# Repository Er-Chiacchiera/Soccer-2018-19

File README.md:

# Soccer-2018-19
Soccer Robot of Pacinotti-Archimede 2018/2019

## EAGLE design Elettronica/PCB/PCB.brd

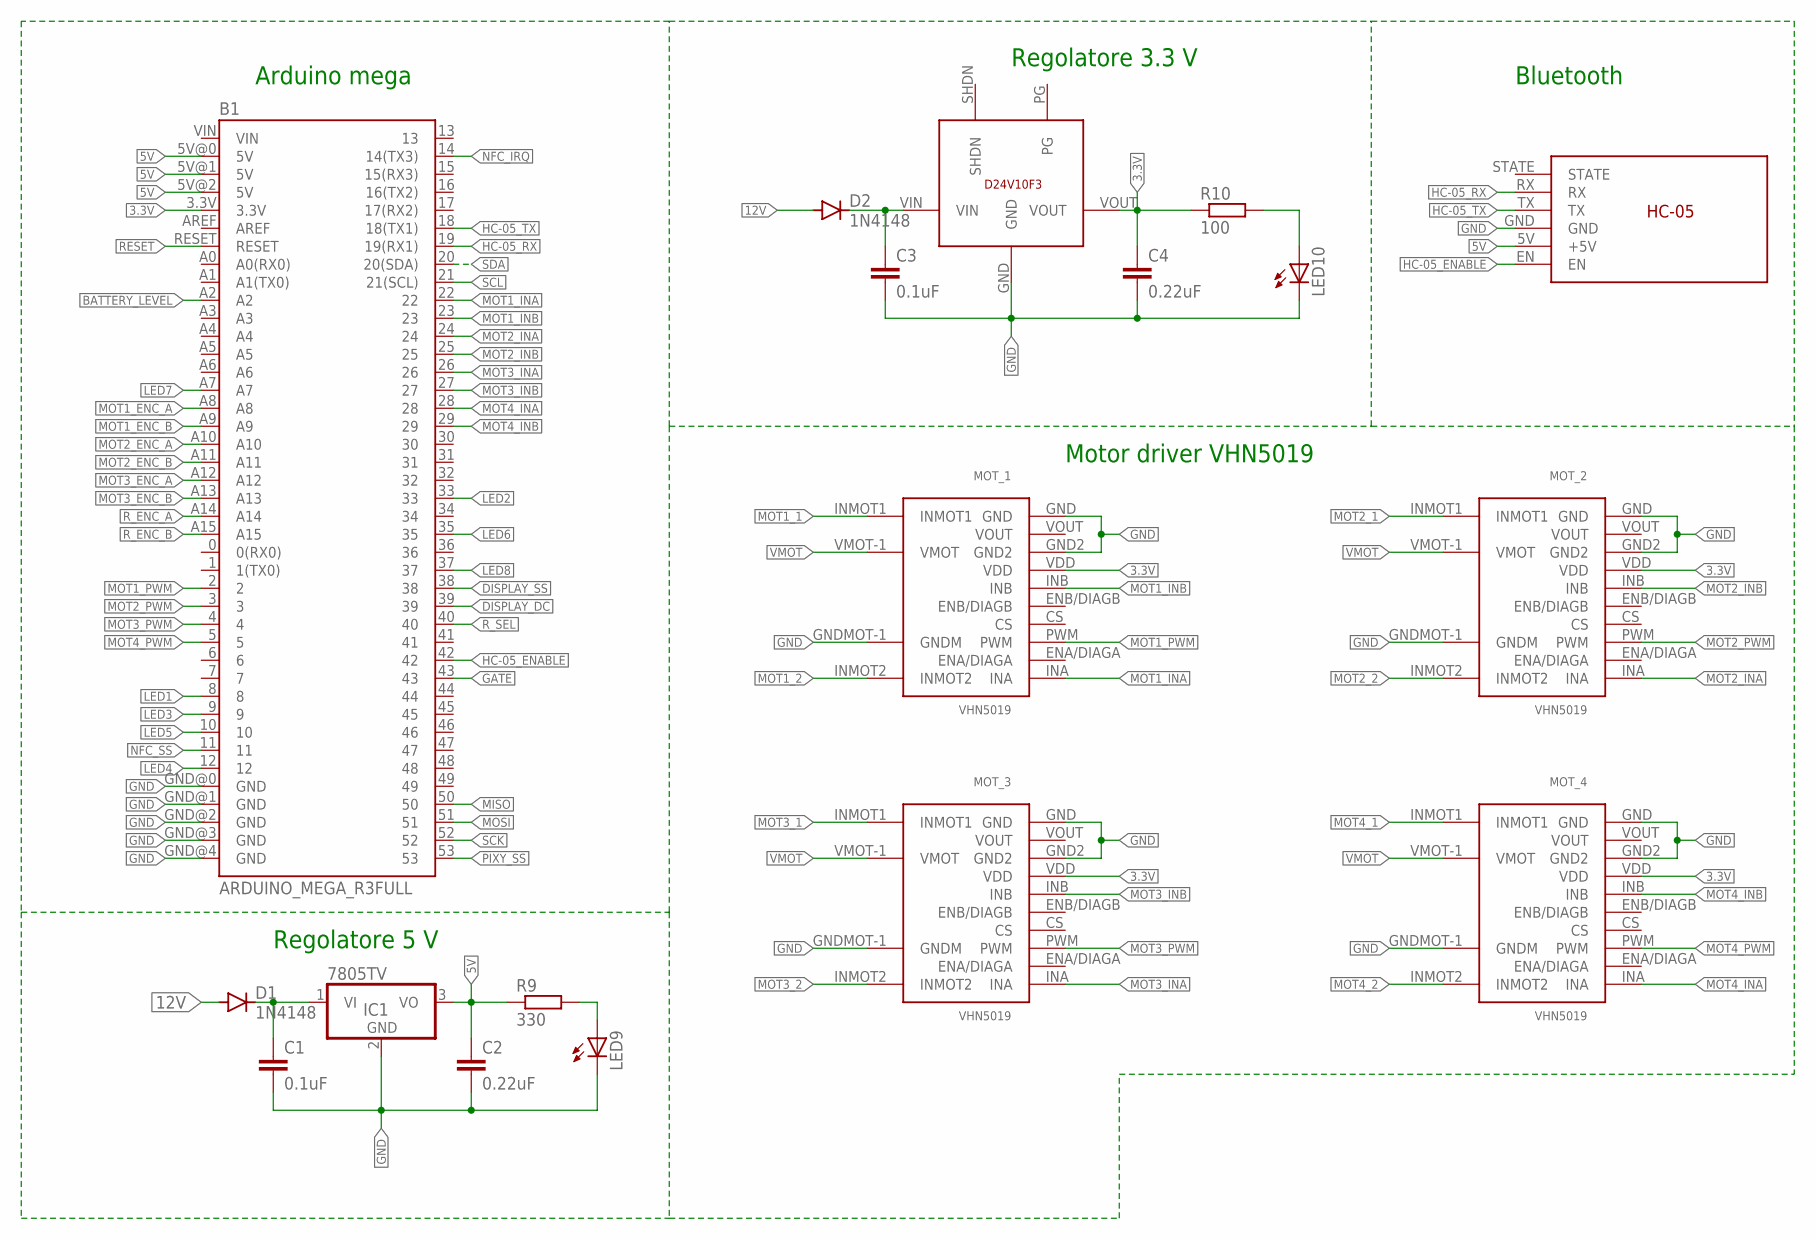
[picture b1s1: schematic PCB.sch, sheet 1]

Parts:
B1: ARDUINO_MEGA_R3FULL; ARDUINO_MEGA
C1, C3: 0.1uF; CAP-PTH-SMALL-KIT
C2, C4: 0.22uF; CAP-PTH-SMALL-KIT
D1, D2: 1N4148; DO41-10
IC1: 7805TV; TO220V
LED9, LED10: LED1206; LED-1206
MOT_1, MOT_2, MOT_3, MOT_4: VHN5019; MOTOR-SHIELD
R9: 330; R1206
R10: 100; R1206
U$1: STEPDOWN_D24V10F3
U$9: HC-05

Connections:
3.3V: B1.3.3V, C4.1, MOT_1.VDD, MOT_2.VDD, MOT_3.VDD, MOT_4.VDD, R10.1, U$1.VOUT; also elsewhere on the board
5V: B1.5V@0 (5V), B1.5V@1 (5V), B1.5V@2 (5V), C2.1, IC1.3 (VO), R9.1, U$9.5V (+5V); also elsewhere on the board
12V: D1.A, D2.A; also elsewhere on the board
BATTERY_LEVEL: B1.A2; also elsewhere on the board
DISPLAY_DC: B1.39; also elsewhere on the board
DISPLAY_SS: B1.38; also elsewhere on the board
GATE: B1.43; also elsewhere on the board
GND: B1.GND@0 (GND), B1.GND@1 (GND), B1.GND@2 (GND), B1.GND@3 (GND), B1.GND@4 (GND), C1.2, C2.2, C3.2, C4.2, IC1.2 (GND), LED9.C, LED10.C, MOT_1.GND, MOT_1.GND2, MOT_1.GNDMOT-1 (GNDM), MOT_2.GND, MOT_2.GND2, MOT_2.GNDMOT-1 (GNDM), MOT_3.GND, MOT_3.GND2, MOT_3.GNDMOT-1 (GNDM), MOT_4.GND, MOT_4.GND2, MOT_4.GNDMOT-1 (GNDM), U$1.GND, U$9.GND; also elsewhere on the board
HC-05_ENABLE: B1.42, U$9.EN
HC-05_RX: B1.19 (19(RX1)), U$9.RX
HC-05_TX: B1.18 (18(TX1)), U$9.TX
LED1: B1.8; also elsewhere on the board
LED2: B1.33; also elsewhere on the board
LED3: B1.9; also elsewhere on the board
LED4: B1.12; also elsewhere on the board
LED5: B1.10; also elsewhere on the board
LED6: B1.35; also elsewhere on the board
LED7: B1.A7; also elsewhere on the board
LED8: B1.37; also elsewhere on the board
MISO: B1.50; also elsewhere on the board
MOSI: B1.51; also elsewhere on the board
MOT1_1: MOT_1.INMOT1; also elsewhere on the board
MOT1_2: MOT_1.INMOT2; also elsewhere on the board
MOT1_ENC_A: B1.A8; also elsewhere on the board
MOT1_ENC_B: B1.A9; also elsewhere on the board
MOT1_INA: B1.22, MOT_1.INA
MOT1_INB: B1.23, MOT_1.INB
MOT1_PWM: B1.2, MOT_1.PWM
MOT2_1: MOT_2.INMOT1; also elsewhere on the board
MOT2_2: MOT_2.INMOT2; also elsewhere on the board
MOT2_ENC_A: B1.A10; also elsewhere on the board
MOT2_ENC_B: B1.A11; also elsewhere on the board
MOT2_INA: B1.24, MOT_2.INA
MOT2_INB: B1.25, MOT_2.INB
MOT2_PWM: B1.3, MOT_2.PWM
MOT3_1: MOT_3.INMOT1; also elsewhere on the board
MOT3_2: MOT_3.INMOT2; also elsewhere on the board
MOT3_ENC_A: B1.A12; also elsewhere on the board
MOT3_ENC_B: B1.A13; also elsewhere on the board
MOT3_INA: B1.26, MOT_3.INA
MOT3_INB: B1.27, MOT_3.INB
MOT3_PWM: B1.4, MOT_3.PWM
MOT4_1: MOT_4.INMOT1
MOT4_2: MOT_4.INMOT2
MOT4_INA: B1.28, MOT_4.INA
MOT4_INB: B1.29, MOT_4.INB
MOT4_PWM: B1.5, MOT_4.PWM
unnamed: LED9.A, R9.2
unnamed: C3.1, D2.C, U$1.VIN
unnamed: LED10.A, R10.2
unnamed: C1.1, D1.C, IC1.1 (VI)
NFC_IRQ: B1.14 (14(TX3)); also elsewhere on the board
NFC_SS: B1.11; also elsewhere on the board
PIXY_SS: B1.53; also elsewhere on the board
RESET: B1.RESET; also elsewhere on the board
R_ENC_A: B1.A14; also elsewhere on the board
R_ENC_B: B1.A15; also elsewhere on the board
R_SEL: B1.40; also elsewhere on the board
SCK: B1.52; also elsewhere on the board
SCL: B1.21 (21(SCL)); also elsewhere on the board
SDA: B1.20 (20(SDA)); also elsewhere on the board
VMOT: MOT_1.VMOT-1 (VMOT), MOT_2.VMOT-1 (VMOT), MOT_3.VMOT-1 (VMOT), MOT_4.VMOT-1 (VMOT); also elsewhere on the board

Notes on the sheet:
Arduino mega
Regolatore 5 V
Motor driver VHN5019
Bluetooth
Regolatore 3.3 V

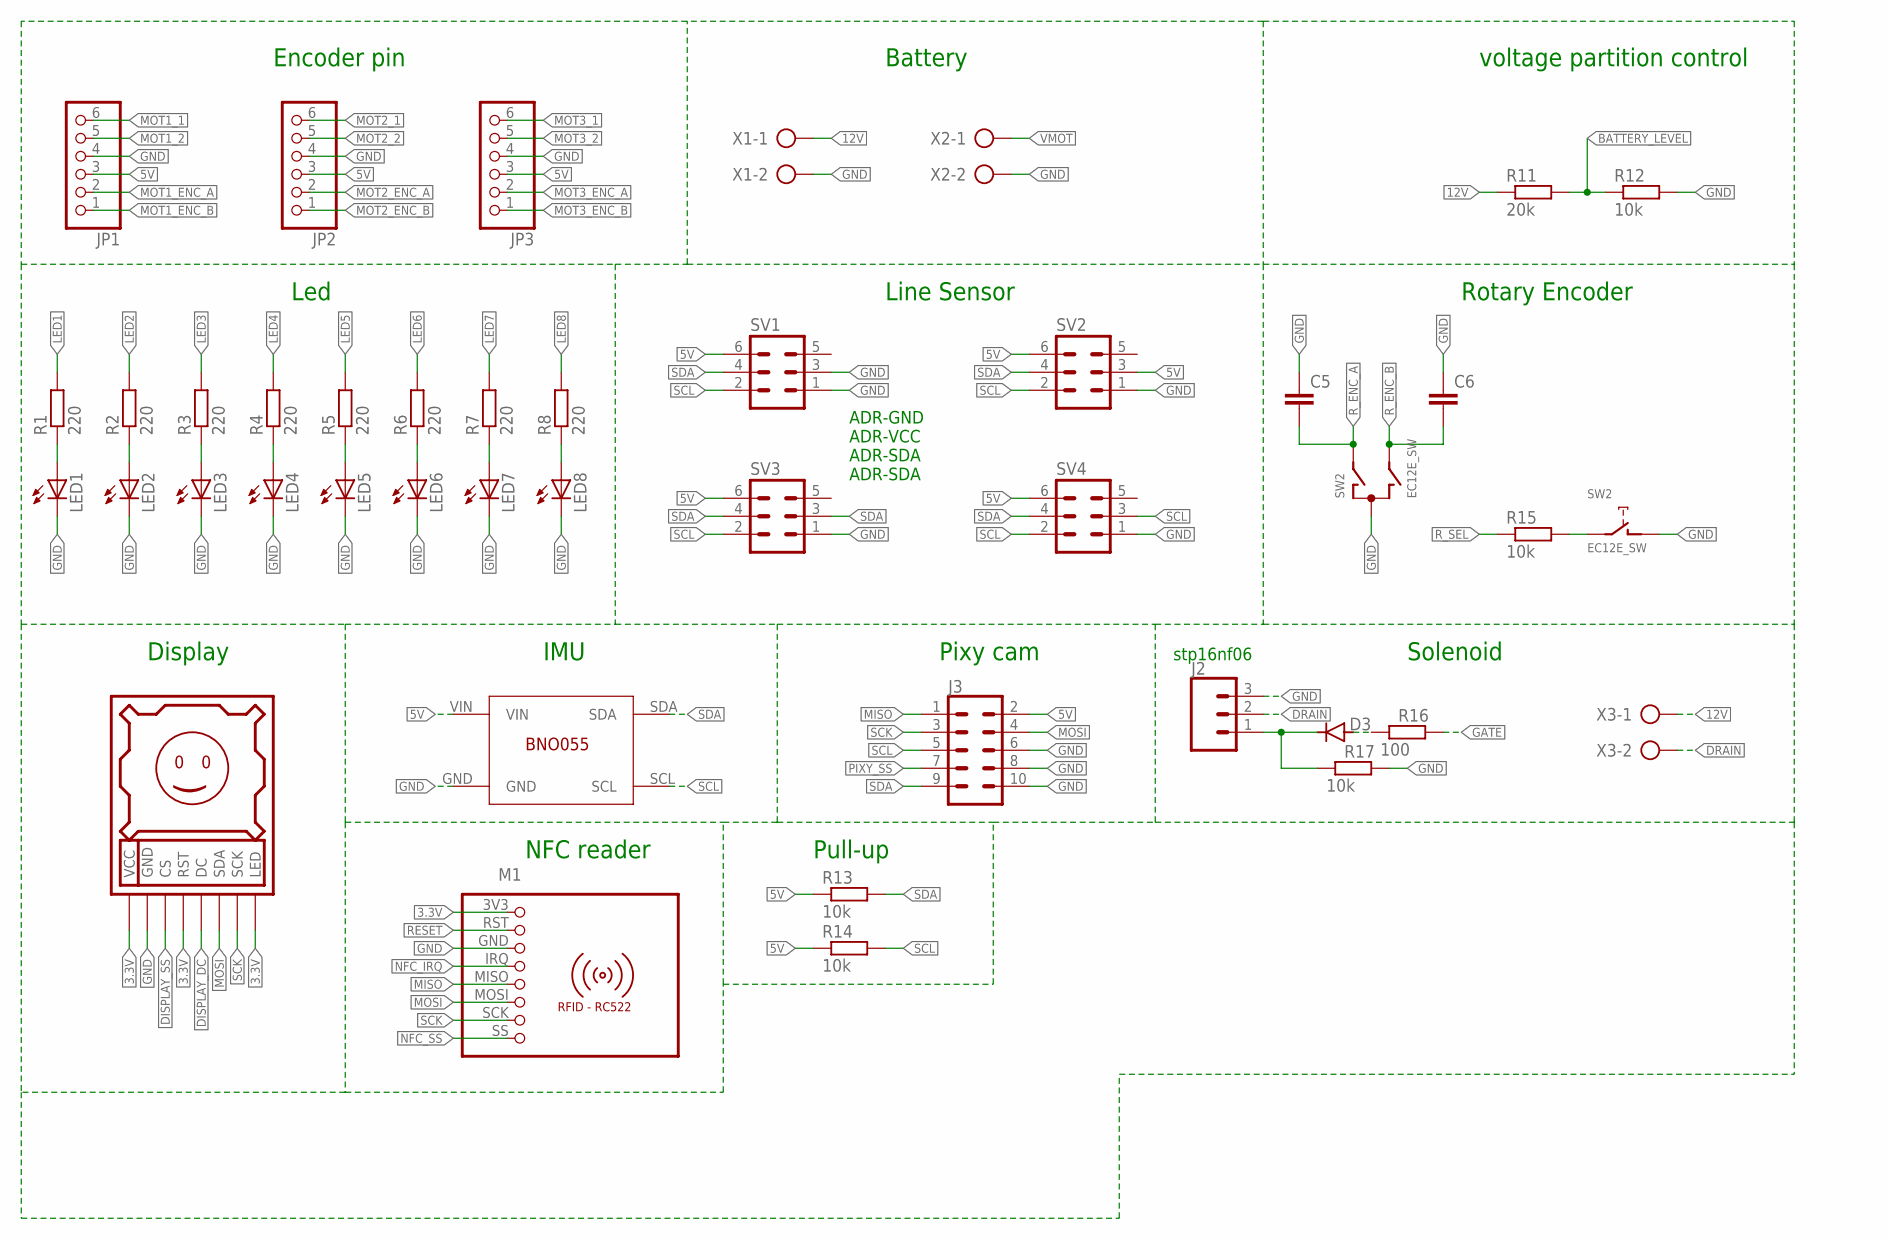
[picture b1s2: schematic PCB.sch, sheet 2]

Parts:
C5, C6: C-EUC1206; C1206
D3: 1N4148; DO35-7
DISPLAY1: DISPLAY128X128
J2: 455-1750-1-ND; 1X03
J3: CONN_05X2PTH; 2X5
JP1, JP2, JP3: PINHD-1X6; 1X06
LED1, LED2, LED3, LED4, LED5, LED6, LED7, LED8: LED1206; LED-1206
M1: RFID-RC522
R1, R2, R3, R4, R5, R6, R7, R8: 220; R1206
R11: 20k; 0204/7
R12: 10k; 0204/7
R13, R14, R15, R17: 10k; R1206
R16: 100; R1206
SV1, SV2, SV3, SV4: MA03-2
SW2: EC12E_SW; ALPS_EC12E_SW
U$8: BNO055; BNO005
X1, X2, X3: AK500/2-H

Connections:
3.3V: DISPLAY1.LED, DISPLAY1.RST, DISPLAY1.VCC, M1.3V3 (1); also elsewhere on the board
5V: J3.2, JP1.3, JP2.3, JP3.3, R13.1, R14.1, SV1.6, SV2.3, SV2.6, SV3.6, SV4.6, U$8.VIN; also elsewhere on the board
12V: R11.1, X1.1, X3.1; also elsewhere on the board
BATTERY_LEVEL: R11.2, R12.1; also elsewhere on the board
DISPLAY_DC: DISPLAY1.DC; also elsewhere on the board
DISPLAY_SS: DISPLAY1.CS; also elsewhere on the board
DRAIN: J2.2, X3.2
GATE: R16.2; also elsewhere on the board
GND: C5.1, C6.1, DISPLAY1.GND, J2.3, J3.6, J3.8, J3.10, JP1.4, JP2.4, JP3.4, LED1.C, LED2.C, LED3.C, LED4.C, LED5.C, LED6.C, LED7.C, LED8.C, M1.GND (3), R12.2, R17.2, SV1.1, SV1.3, SV2.1, SV3.1, SV4.1, SW2.C, SW2.D (1), U$8.GND, X1.2, X2.2; also elsewhere on the board
LED1: R1.2; also elsewhere on the board
LED2: R2.2; also elsewhere on the board
LED3: R3.2; also elsewhere on the board
LED4: R4.2; also elsewhere on the board
LED5: R5.2; also elsewhere on the board
LED6: R6.2; also elsewhere on the board
LED7: R7.2; also elsewhere on the board
LED8: R8.2; also elsewhere on the board
MISO: J3.1, M1.MISO (5); also elsewhere on the board
MOSI: DISPLAY1.SDA, J3.4, M1.MOSI (6); also elsewhere on the board
MOT1_1: JP1.6; also elsewhere on the board
MOT1_2: JP1.5; also elsewhere on the board
MOT1_ENC_A: JP1.2; also elsewhere on the board
MOT1_ENC_B: JP1.1; also elsewhere on the board
MOT2_1: JP2.6; also elsewhere on the board
MOT2_2: JP2.5; also elsewhere on the board
MOT2_ENC_A: JP2.2; also elsewhere on the board
MOT2_ENC_B: JP2.1; also elsewhere on the board
MOT3_1: JP3.6; also elsewhere on the board
MOT3_2: JP3.5; also elsewhere on the board
MOT3_ENC_A: JP3.2; also elsewhere on the board
MOT3_ENC_B: JP3.1; also elsewhere on the board
unnamed: D3.C, J2.1, R17.1
unnamed: D3.A, R16.1
unnamed: LED1.A, R1.1
unnamed: LED2.A, R2.1
unnamed: LED3.A, R3.1
unnamed: LED4.A, R4.1
unnamed: LED5.A, R5.1
unnamed: LED6.A, R6.1
unnamed: LED7.A, R7.1
unnamed: LED8.A, R8.1
unnamed: R15.2, SW2.E (2)
NFC_IRQ: M1.IRQ (4); also elsewhere on the board
NFC_SS: M1.SS (8); also elsewhere on the board
PIXY_SS: J3.7; also elsewhere on the board
RESET: M1.RST (2); also elsewhere on the board
R_ENC_A: C5.2, SW2.A; also elsewhere on the board
R_ENC_B: C6.2, SW2.B; also elsewhere on the board
R_SEL: R15.1; also elsewhere on the board
SCK: DISPLAY1.SCK, J3.3, M1.SCK (7); also elsewhere on the board
SCL: J3.5, R14.2, SV1.2, SV2.2, SV3.2, SV4.2, SV4.3, U$8.SCL; also elsewhere on the board
SDA: J3.9, R13.2, SV1.4, SV2.4, SV3.3, SV3.4, SV4.4, U$8.SDA; also elsewhere on the board
VMOT: X2.1; also elsewhere on the board

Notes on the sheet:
Encoder pin
Battery
Led
ADR-GND ADR-VCC ADR-SDA ADR-SDA
voltage partition control
Rotary Encoder
Line Sensor
Display
Solenoid
IMU
Pixy cam
NFC reader
stp16nf06
Pull-up

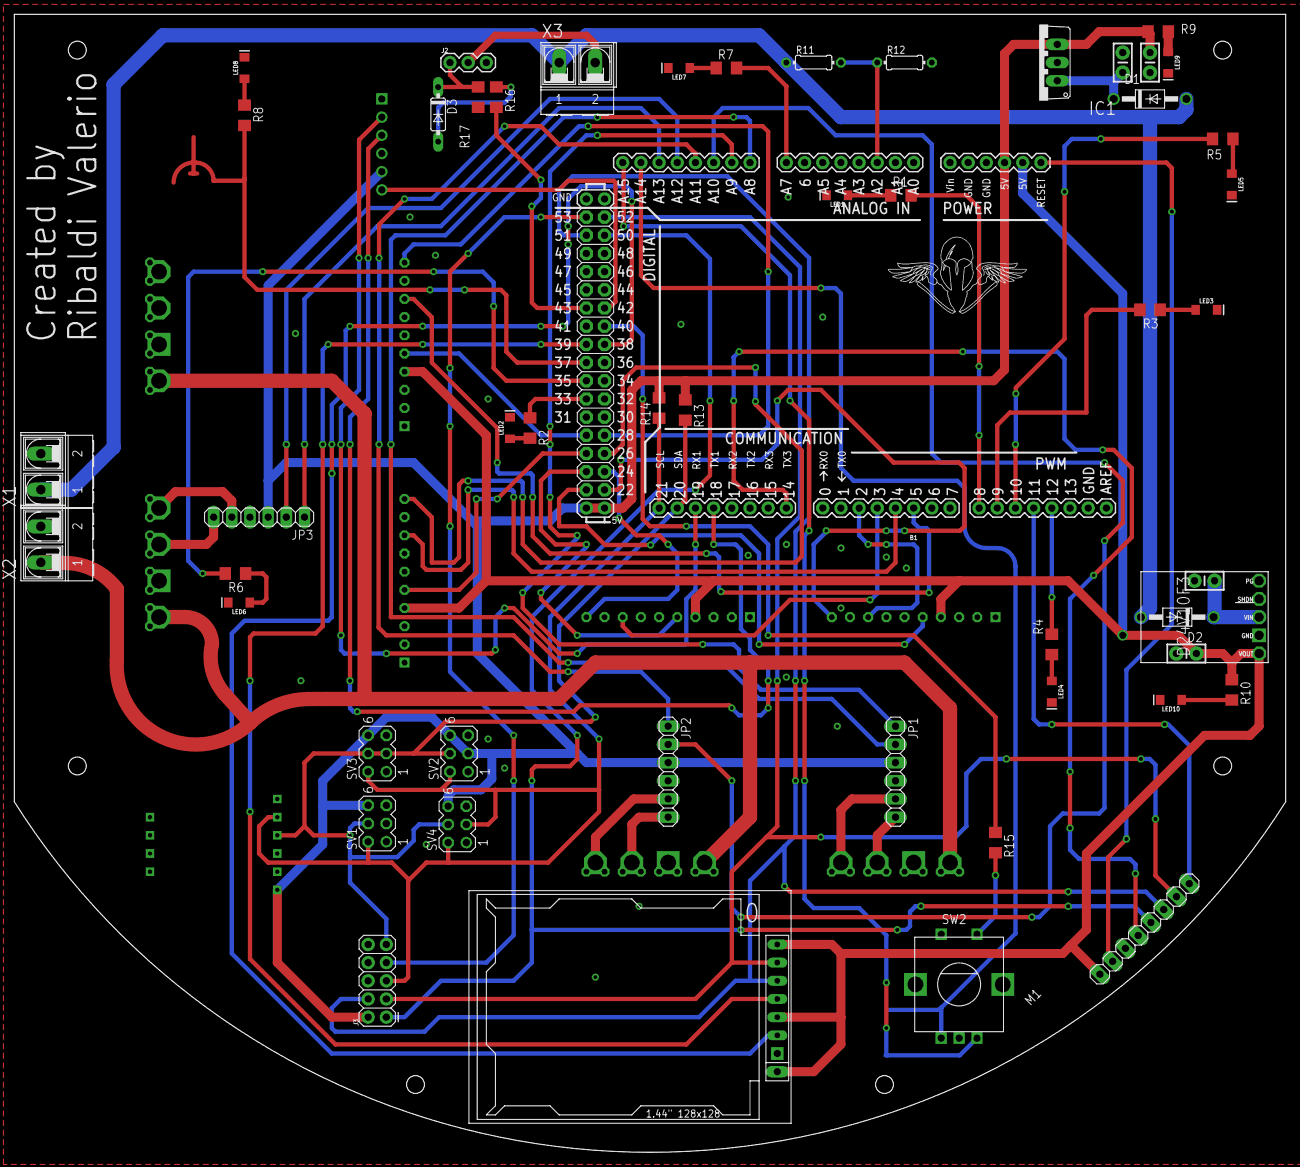
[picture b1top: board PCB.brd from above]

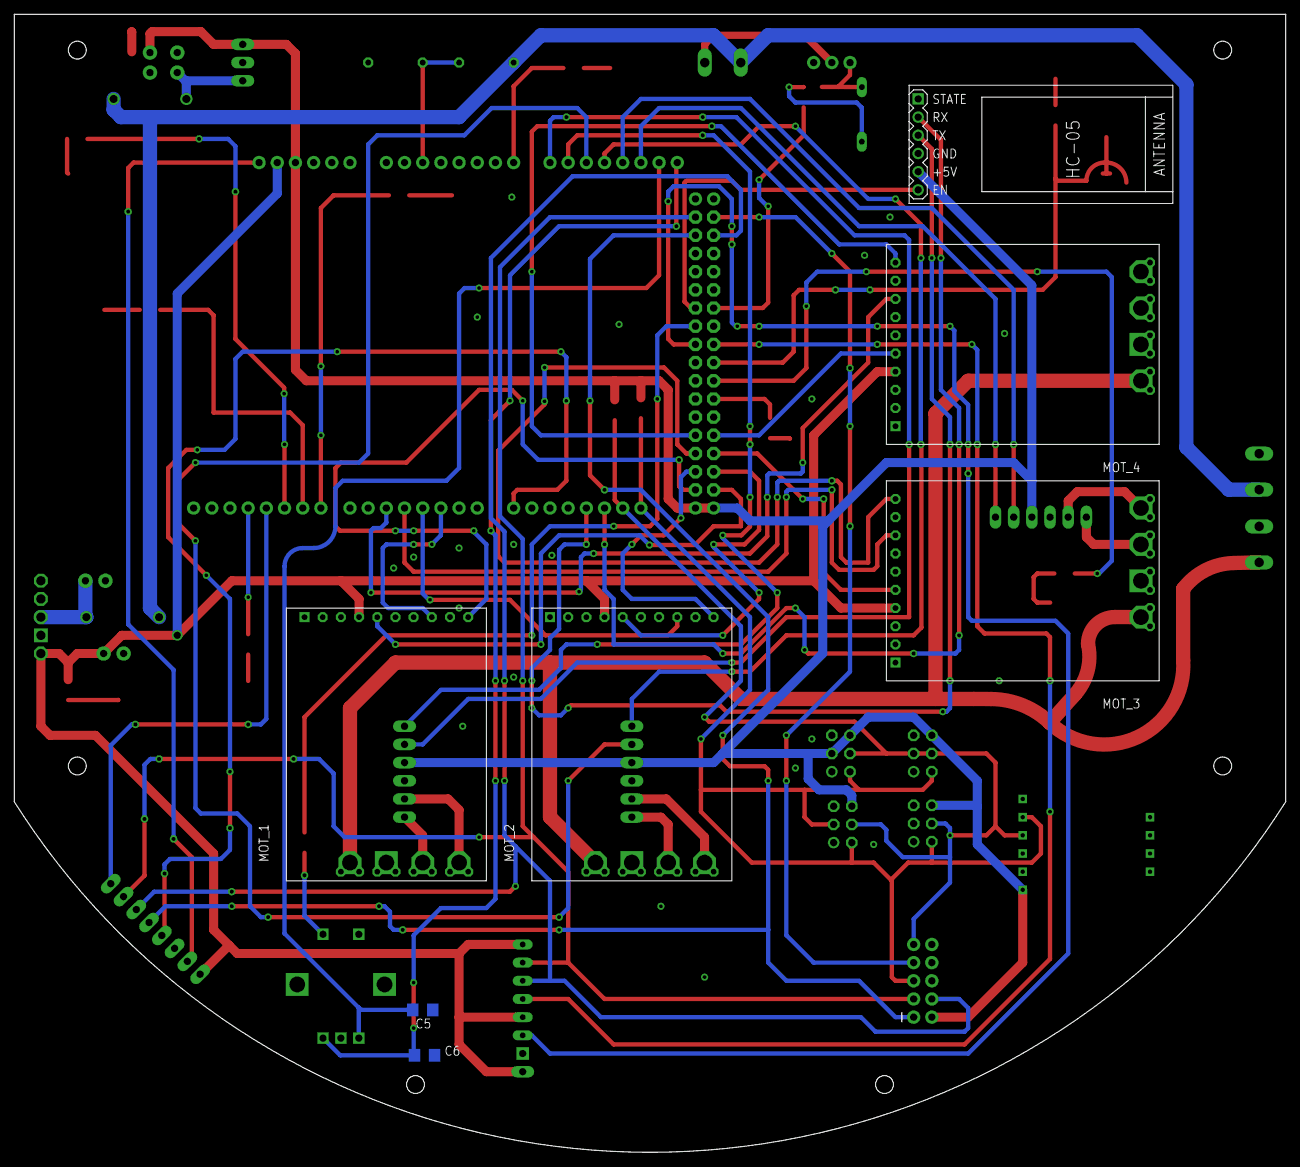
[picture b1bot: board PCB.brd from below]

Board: 2 copper layers, 177.6 x 159.0 mm, 60 parts (7 on the bottom side), 72 nets.

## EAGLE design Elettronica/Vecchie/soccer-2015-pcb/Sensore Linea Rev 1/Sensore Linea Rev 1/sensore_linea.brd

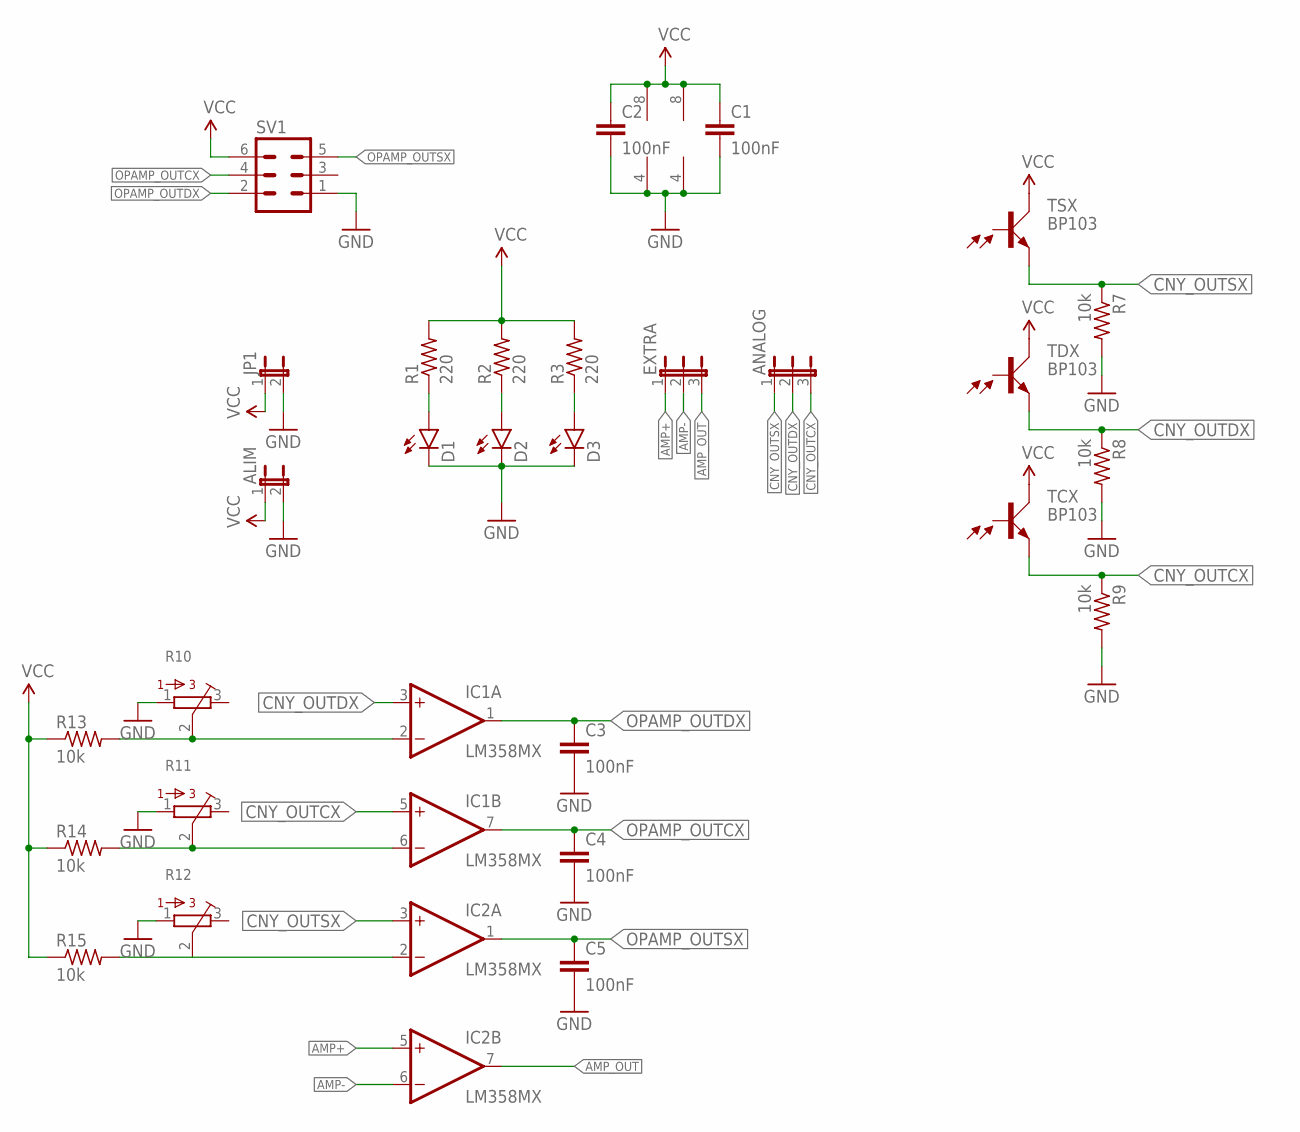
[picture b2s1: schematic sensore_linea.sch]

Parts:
ALIM: JP1E; JP1
ANALOG: JP2E; JP2
C1, C2, C3, C4, C5: 100nF; C2.5-2
D1, D2, D3: LED3MM
EXTRA: JP2E; JP2
IC1, IC2: LM358MX; SO08
JP1: JP1E; JP1
R1, R2, R3: 220; 0207/7
R7, R8, R9, R13, R14, R15: 10k; 0207/7
R10, R11, R12: 3386-J; 3386J
SV1: MA03-2
TCX: BP103
TDX: BP103
TSX: BP103

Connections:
AMP+: EXTRA.1, IC2.5 (+IN)
AMP-: EXTRA.2, IC2.6 (-IN)
AMP_OUT: EXTRA.3, IC2.7 (OUT)
CNY_OUTCX: ANALOG.3, IC1.5 (+IN), R9.1, TCX.E
CNY_OUTDX: ANALOG.2, IC1.3 (+IN), R8.1, TDX.E
CNY_OUTSX: ANALOG.1, IC2.3 (+IN), R7.1, TSX.E
GND: ALIM.2, C1.2, C2.2, C3.2, C4.2, C5.2, D1.K (C), D2.K (C), D3.K (C), IC1.4 (V-), IC2.4 (V-), JP1.2, R7.2, R8.2, R9.2, R10.1, R11.1, R12.1, SV1.1
unnamed: D1.A, R1.1
unnamed: D2.A, R2.1
unnamed: D3.A, R3.1
unnamed: IC1.2 (-IN), R10.2, R13.2
unnamed: IC1.6 (-IN), R11.2, R14.2
unnamed: IC2.2 (-IN), R12.2, R15.2
OPAMP_OUTCX: C4.1, IC1.7 (OUT), SV1.4
OPAMP_OUTDX: C3.1, IC1.1 (OUT), SV1.2
OPAMP_OUTSX: C5.1, IC2.1 (OUT), SV1.5
VCC: ALIM.1, C1.1, C2.1, IC1.8 (V+), IC2.8 (V+), JP1.1, R1.2, R2.2, R3.2, R13.1, R14.1, R15.1, SV1.6, TCX.C, TDX.C, TSX.C

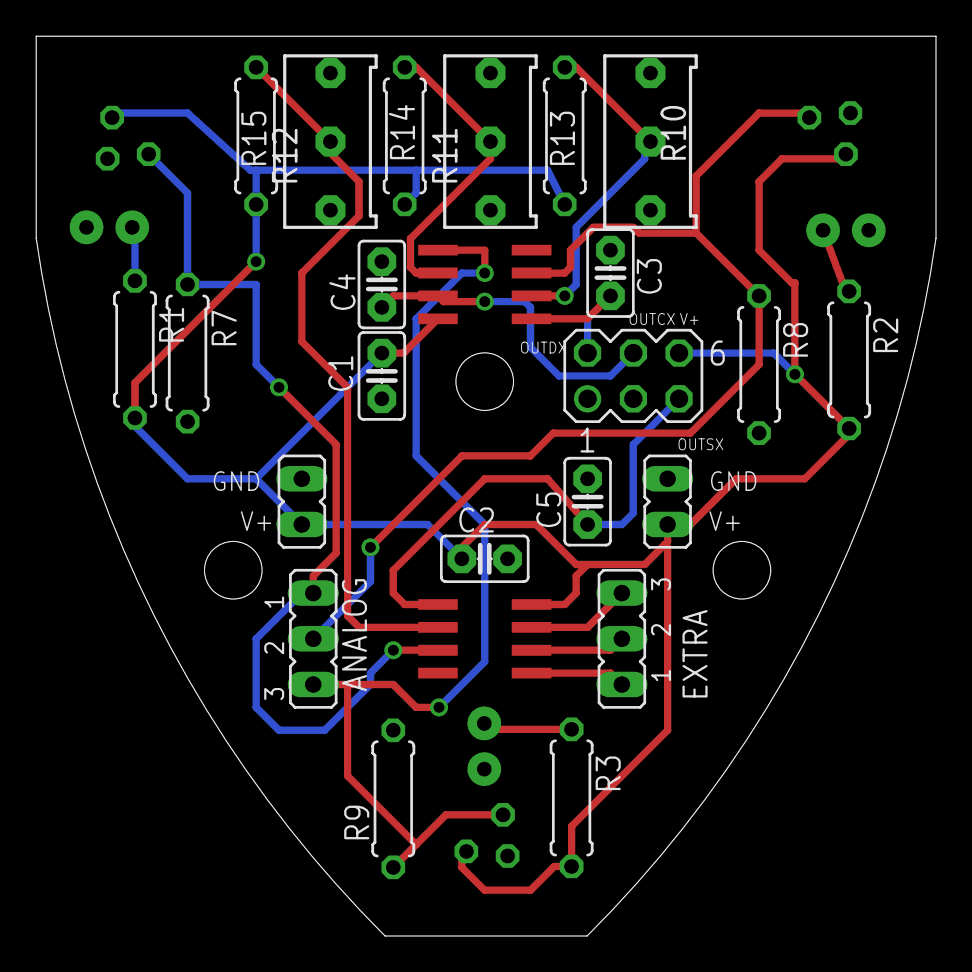
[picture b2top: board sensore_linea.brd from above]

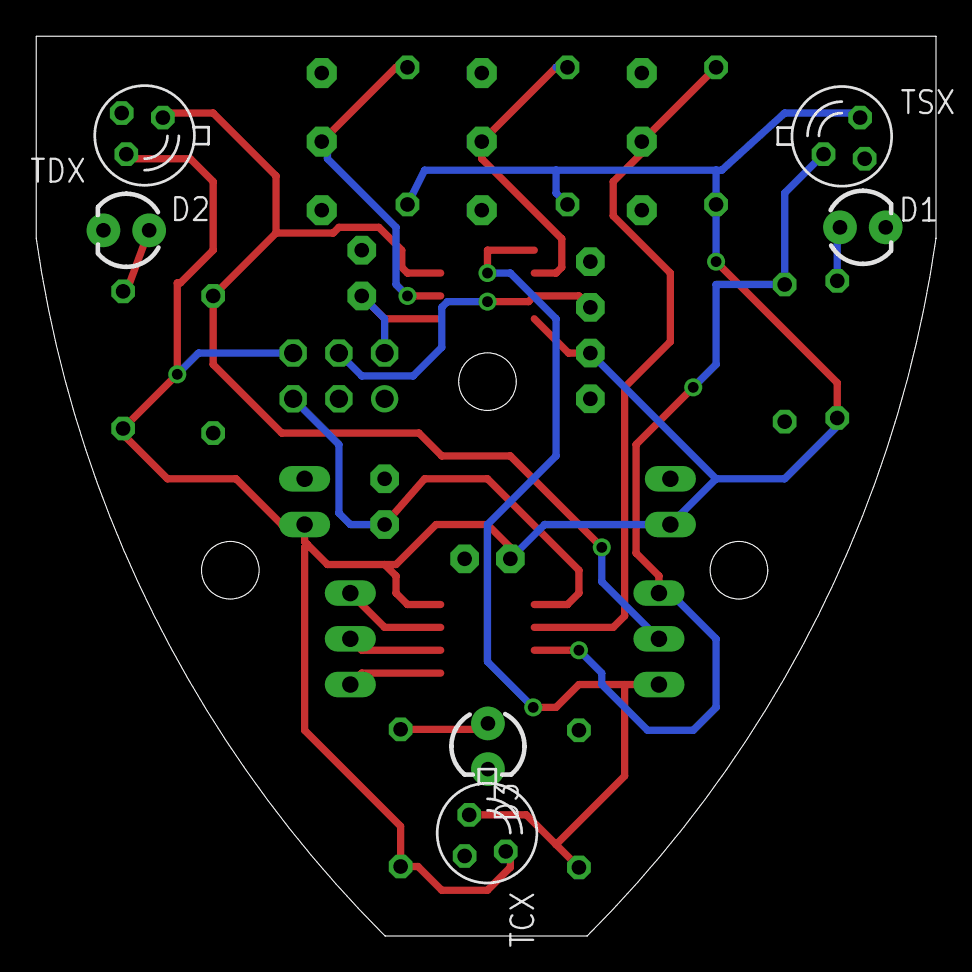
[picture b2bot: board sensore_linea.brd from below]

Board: 2 copper layers, 50.0 x 50.0 mm, 30 parts (6 on the bottom side), 17 nets.

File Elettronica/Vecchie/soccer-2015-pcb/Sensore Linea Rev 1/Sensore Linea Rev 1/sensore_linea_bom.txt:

Partlist exported from C:/Users/Punturo/Dropbox/Calciatore/Calciatore 2015/Phoenix rev 2/Schemi e boards/Sensore Linea Rev 1/sensore_linea.sch at 26/01/2016 11:30:23

Part   Value   Device      Package Description                      MF MPN OC_FARNELL OC_NEWARK
ALIM           JP1E        JP1     JUMPER                                                      
ANALOG         JP2E        JP2     JUMPER                                                      
C1     100nF   C2.5/2      C2.5-2  CAPACITOR                                                   
C2     100nF   C2.5/2      C2.5-2  CAPACITOR                                                   
C3     100nF   C2.5/2      C2.5-2  CAPACITOR                                                   
C4     100nF   C2.5/2      C2.5-2  CAPACITOR                                                   
C5     100nF   C2.5/2      C2.5-2  CAPACITOR                                                   
D1             LED3MM      LED3MM  LEDs                                                        
D2             LED3MM      LED3MM  LEDs                                                        
D3             LED3MM      LED3MM  LEDs                                                        
EXTRA          JP2E        JP2     JUMPER                                                      
IC1    LM358MX LM358MX     SO08    OP AMP also LM158; LM258; LM2904                            
IC2    LM358MX LM358MX     SO08    OP AMP also LM158; LM258; LM2904                            
JP1            JP1E        JP1     JUMPER                                                      
R1     220     R-US_0207/7 0207/7  RESISTOR, American symbol                                   
R2     220     R-US_0207/7 0207/7  RESISTOR, American symbol                                   
R3     220     R-US_0207/7 0207/7  RESISTOR, American symbol                                   
R7     10k     R-US_0207/7 0207/7  RESISTOR, American symbol                                   
R8     10k     R-US_0207/7 0207/7  RESISTOR, American symbol                                   
R9     10k     R-US_0207/7 0207/7  RESISTOR, American symbol                                   
R10            3386-J      3386J   3386 Series                                                 
R11            3386-J      3386J   3386 Series                                                 
R12            3386-J      3386J   3386 Series                                                 
R13    10k     R-US_0207/7 0207/7  RESISTOR, American symbol                                   
R14    10k     R-US_0207/7 0207/7  RESISTOR, American symbol                                   
R15    10k     R-US_0207/7 0207/7  RESISTOR, American symbol                                   
SV1            MA03-2      MA03-2  PIN HEADER                              unknown    unknown  
TCX    BP103   BP103       BP103   PHOTO TRANSISTOR                        unknown    unknown  
TDX    BP103   BP103       BP103   PHOTO TRANSISTOR                        unknown    unknown  
TSX    BP103   BP103       BP103   PHOTO TRANSISTOR                        unknown    unknown

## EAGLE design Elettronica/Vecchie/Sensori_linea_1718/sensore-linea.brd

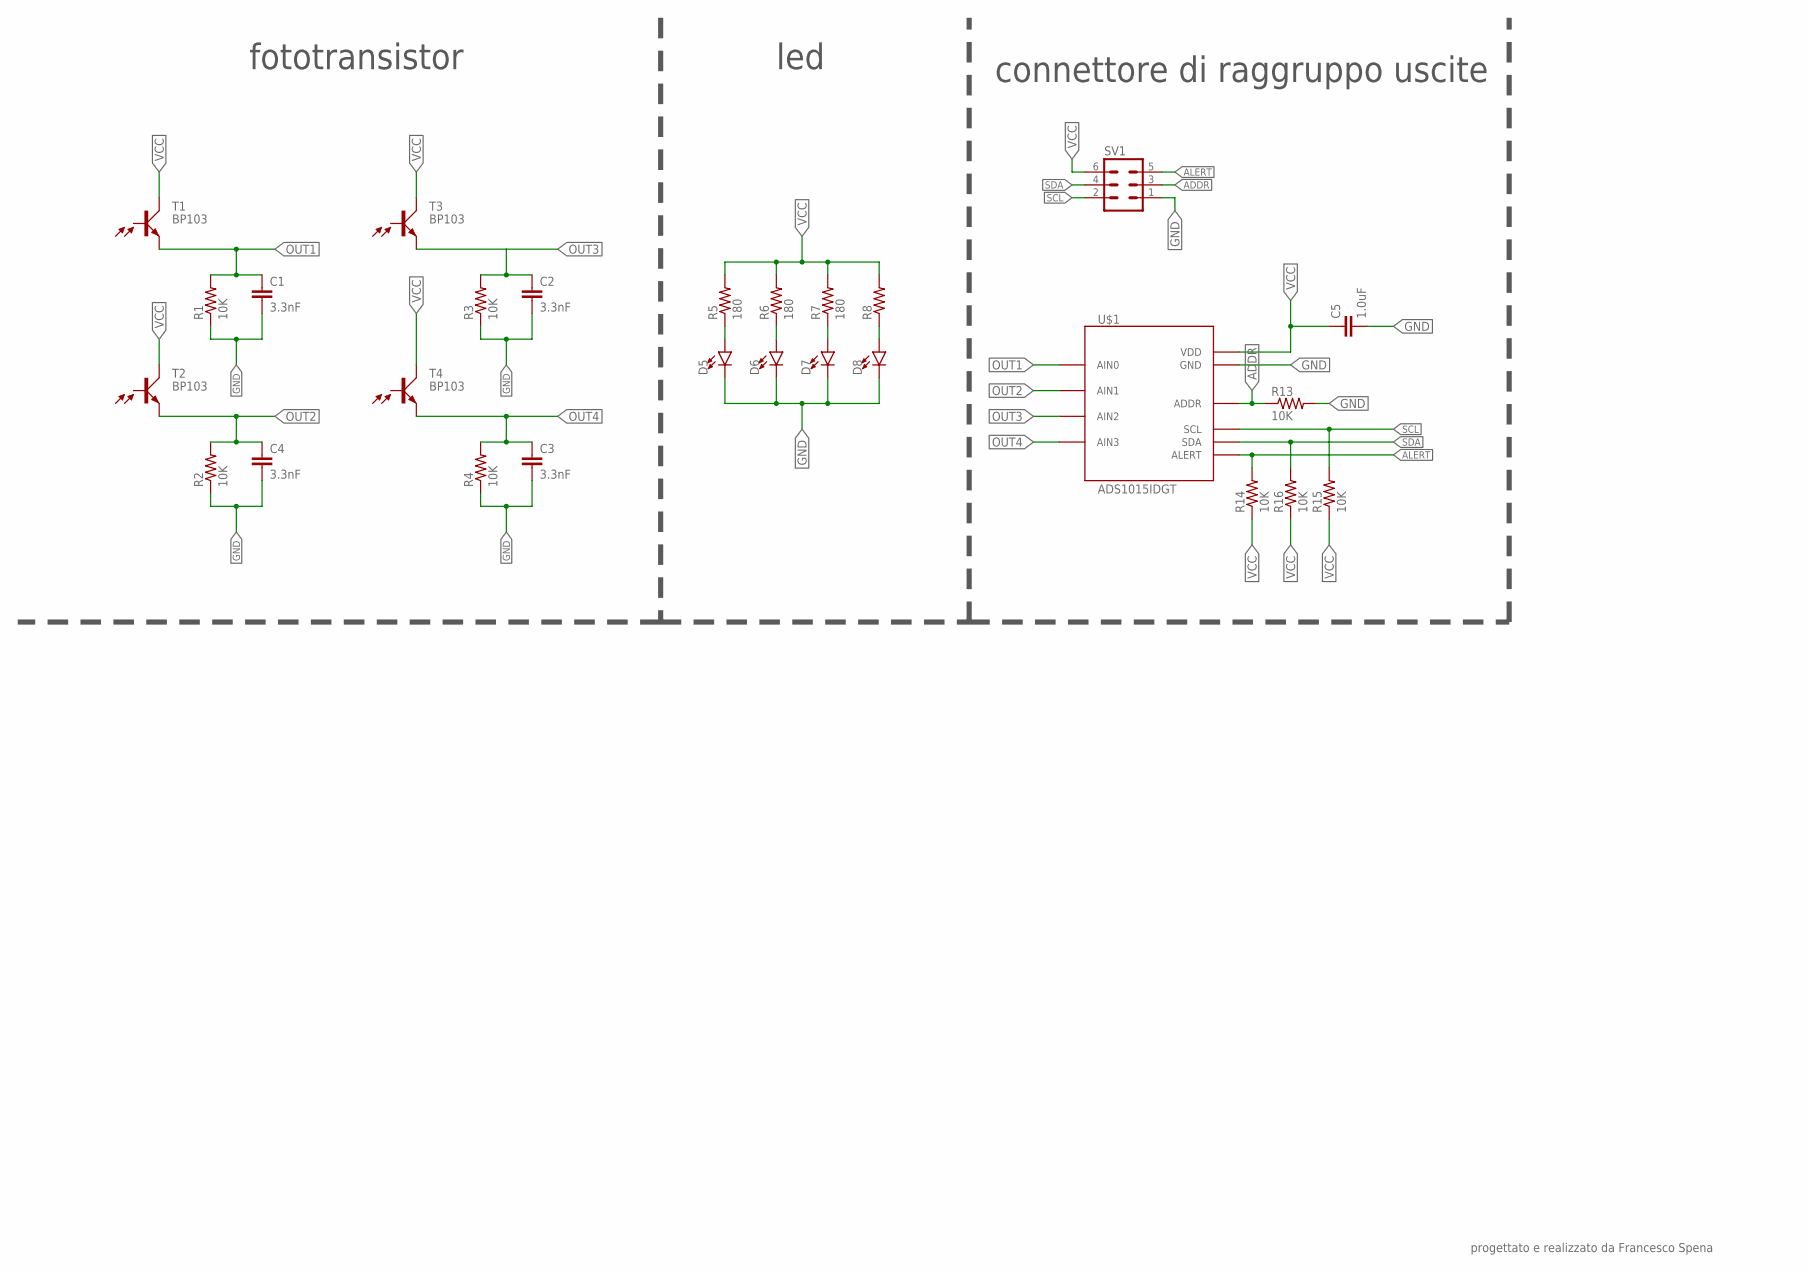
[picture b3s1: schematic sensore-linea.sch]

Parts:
C1, C2, C3, C4: 3.3nF; 0603
C5: 1.0uF; 0402
D5, D6, D7, D8: LED3MM; LED_3MM
R1, R2, R3, R4, R13, R14, R15, R16: 10K; 0204/7
R5, R6, R7: 180; 0204/7
R8: R-US_0204/7; 0204/7
SV1: MA03-2
T1, T2, T3, T4: BP103
U$1: ADS1015IDGT; MSOP10_0.5

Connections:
ADDR: R13.1, SV1.3, U$1.1 (ADDR)
ALERT: R14.2, SV1.5, U$1.2 (ALERT)
GND: C1.2, C2.2, C3.2, C4.2, C5.2, D5.K (C), D6.K (C), D7.K (C), D8.K (C), R1.1, R2.1, R3.1, R4.1, R13.2, SV1.1, U$1.3 (GND)
unnamed: D5.A, R5.1
unnamed: D6.A, R6.1
unnamed: D7.A, R7.1
unnamed: D8.A, R8.1
OUT1: C1.1, R1.2, T1.E, U$1.4 (AIN0)
OUT2: C4.1, R2.2, T2.E, U$1.5 (AIN1)
OUT3: C2.1, R3.2, T3.E, U$1.6 (AIN2)
OUT4: C3.1, R4.2, T4.E, U$1.7 (AIN3)
SCL: R15.2, SV1.2, U$1.10 (SCL)
SDA: R16.2, SV1.4, U$1.9 (SDA)
VCC: C5.1, R5.2, R6.2, R7.2, R8.2, R14.1, R15.1, R16.1, SV1.6, T1.C, T2.C, T3.C, T4.C, U$1.8 (VDD)

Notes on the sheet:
fototransistor
led
connettore di raggruppo uscite
progettato e realizzato da Francesco Spena

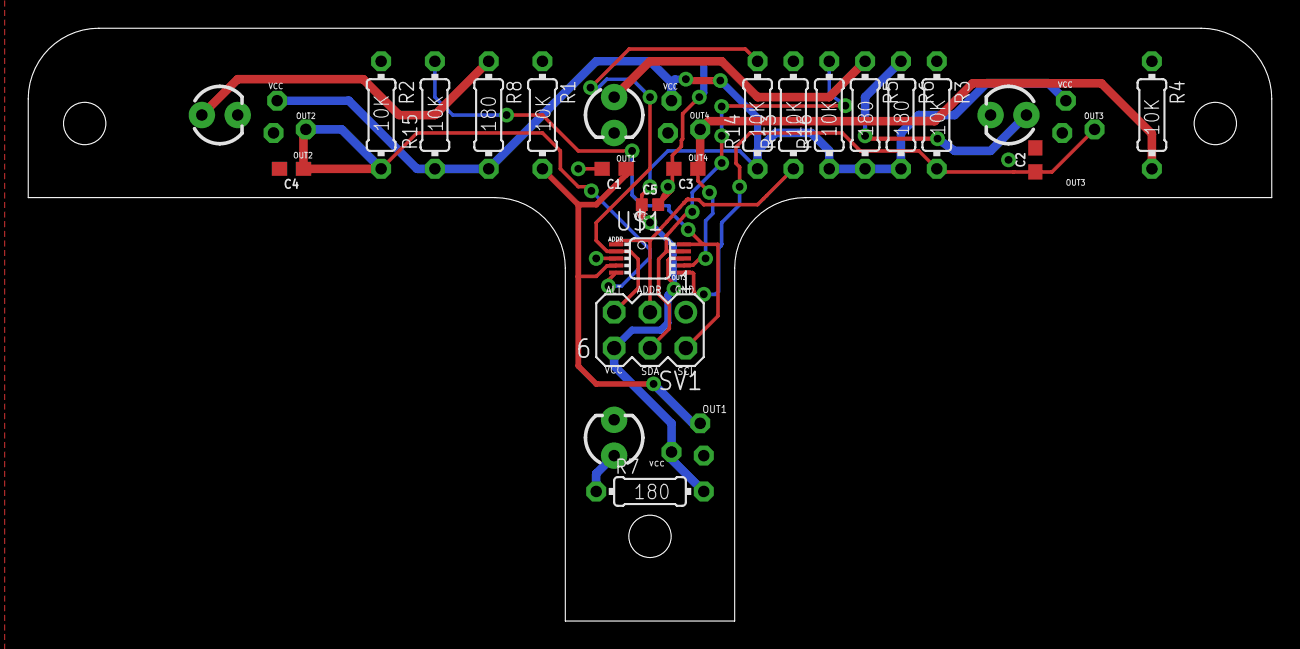
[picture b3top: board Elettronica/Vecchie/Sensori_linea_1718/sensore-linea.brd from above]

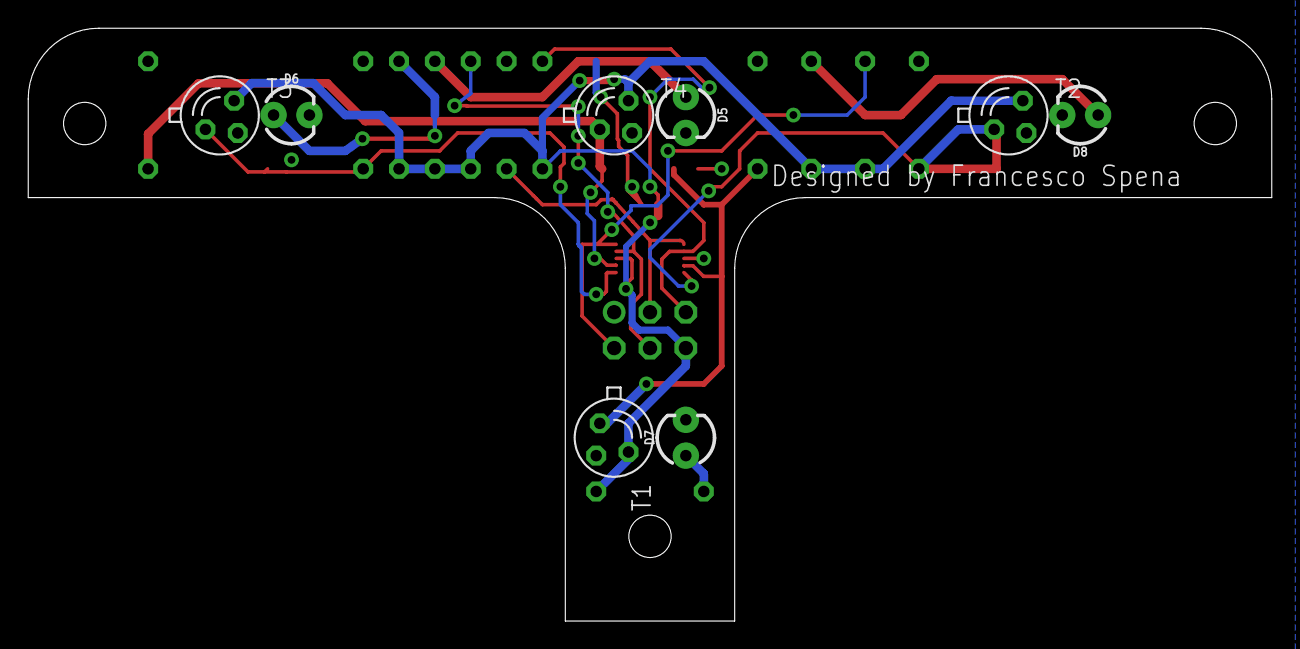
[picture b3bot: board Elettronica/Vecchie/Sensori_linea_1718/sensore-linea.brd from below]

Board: 2 copper layers, 88.1 x 42.0 mm, 27 parts (8 on the bottom side), 14 nets.

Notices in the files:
parts and their libraries:
SparkFun-Boards: Licensing: Creative Commons ShareAlike 4.0 International - https://creativecommons.org/licenses/by-sa/4.0
